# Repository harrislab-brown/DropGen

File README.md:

## Welcome to DropGen! A droplet on demand generator for research applications developed in the Harris Lab at Brown University

DropGen uses a fluid reservoir and a piezoelectric buzzer to precisely and repeatably dispense small droplets on demand. 
This new version of the Harris Lab DropGen is designed to be 3D printed using filament based FDM printers. Harris Lab has developed a custom printed circuit board to make assembly and use of DropGen as easy as possible, including adding the ability to control the height of DropGen with a commonly available stepper motor driven linear actuator. 

### WIKI:
Complete build documentation and user guide for DropGen can be found under the [Wiki](https://github.com/harrislab-brown/Filament_DropGen/wiki) tab of this repository.

### CAD: 
The CAD directory contains design files for the droplet generator 3D printed parts and the custom PCB. 
Cad files are available as a .f3z Fusion360 archive file, as well as program agnostic .step files for modification in parametric cad software. All parts that require 3D printing are also available in .stl format which can be used with all modern 3D printing slicers. 

The DropGenPCB directory contains project files for the printed circuit board. The PCB was designed using KiCad 8. Production files ready to send to JLCPCB are available here as well (see wiki for details). 

### CODE: 
DropGen is controlled by a web based GUI running on an ESP32-S3 development board. The wiki contains instructions on how to set up the environment required to flash the ESP32 firmware. 

### Documentation: 
This directory contains image and video assets used in the wiki. 

### Credit: 
If you use or adapt the device for academic publication, please cite this repository as well as the preceding works:
* N. Ionkin and D. M. Harris.  Note: A versatile 3D-printed droplet-on-demand generator. Review of Scientific Instruments. 2018; 89 (11) : 116103. [doi.org/10.1063/1.5054400](doi.org/10.1063/1.5054400)
* D. M. Harris, T. Liu and J. W. M. Bush. A low-cost, precise piezoelectric droplet-on-demand generator. Experiments in Fluids. 2015; 56 (4). [dx.doi.org/10.1007/s00348-015-1950-6](dx.doi.org/10.1007/s00348-015-1950-6)

Happy building!

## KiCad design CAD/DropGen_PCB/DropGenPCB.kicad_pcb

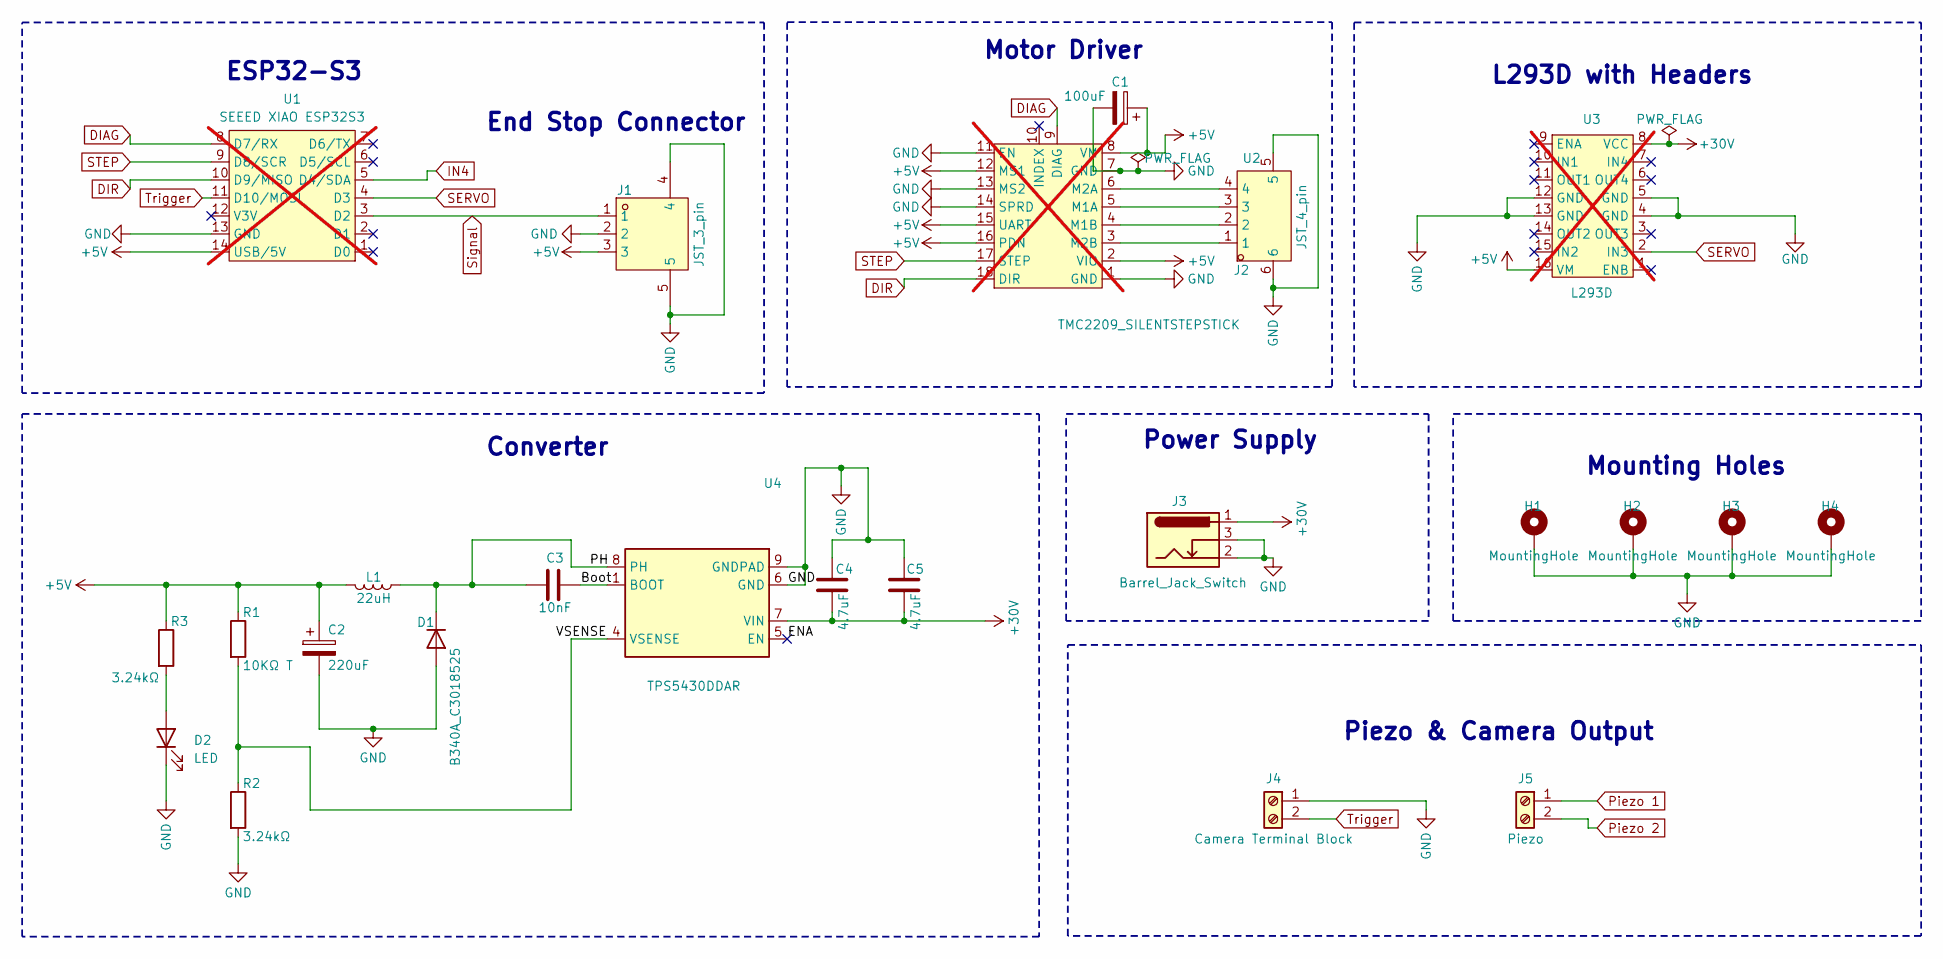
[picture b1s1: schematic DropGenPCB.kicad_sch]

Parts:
C1: 100uF; C_Elec_6.3x7.7; Manufac. Part RVT1V101M0607; LCSC C72478
C2: 220uF; CP_EIA-6032-15_Kemet-U; Manufac. Part TPSC107K010R0100; LCSC C183034
C3: 10nF; C_0805_2012Metric; Manufac. Part 08055C103KAT2A; LCSC C128911
C4, C5: 4.7uF; C_1210_3225Metric; Manufac. Part CS3225X7R106K500NRL; LCSC C2918502
D1: B340A_C3018525; D_SMC; Manufac. Part B560C-13-F; LCSC C85100
D2: LED; LED_0603_1608Metric; Manufac. Part KT-0603R; LCSC C2286
H1, H2, H3, H4: MountingHole; MountingHole_3.2mm_M3_DIN965_Pad
J1: JST_3_pin; 3_pin_jst; Manufac. Part S3B-XH-SM4-TB(LF)(SN); LCSC C5306495
J2: JST_4_pin; 4_pin_jst; Manufac. Part S4B-XH-SM4-TB(LF)(SN); LCSC C161861
J3: Barrel_Jack_Switch; BarrelJack_GCT_DCJ200-10-A_Horizontal; Manufac. Part DC-470-2.1GP; LCSC C194407
J4: Camera Terminal Block; terminal_block; Manufac. Part XY115A-5.0-2P; LCSC C784935
J5: Piezo; terminal_block; Manufac. Part XY115A-5.0-2P; LCSC C784935
L1: 22uH; L_Vishay_IHLP-4040; Manufac. Part IHLP4040DZER220M11; LCSC C845072
R1: 10KΩ T; R_0402_1005Metric_Pad0.72x0.64mm_HandSolder; Manufac. Part RC0201FR-0710KL; LCSC C25744
R2, R3: 3.24kΩ; R_0603_1608Metric; Manufac. Part CRCW06033K24FKEA; LCSC C844165
U1: SEEED XIAO ESP32S3; ESP32S3; Manufac. Part 113991114; not fitted
U2: TMC2209_SILENTSTEPSTICK; MC2209 numbers; Manufac. Part 787794452214; not fitted
U3: L293D; Manufac. Part L293DN; LCSC C434590; not fitted
U4: TPS5430DDAR; TI_SO-PowerPAD-8_ThermalVias; Manufac. Part TPS5430DDAR; LCSC C9864

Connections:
+5V: C1.1, C2.1, J1.3, L1.2, R1.1, R3.1, U1.14 (USB/5V), U2.2 (VIO), U2.8 (VM), U2.12 (MS1), U2.15 (UART), U2.16 (PDN), U3.16 (VM)
+30V: C4.2, C5.2, J3.1, U3.8 (VCC), U4.7 (VIN)
/Boot: C3.2, U4.1 (BOOT)
/ENA: U4.5 (EN)
/PH: C3.1, D1.1 (K), L1.1, U4.8 (PH)
/VSENSE: R1.2, R2.1, U4.4 (VSENSE)
DIAG: U1.8 (D7/RX), U2.9 (DIAG)
DIR: U1.10 (D9/MISO), U2.18 (DIR)
GND: C1.2, C2.2, C4.1, C5.1, D1.2 (A), D2.1 (K), H1.1, H2.1, H3.1, H4.1, J1.2, J1.4, J1.5, J2.5, J2.6, J3.2, J3.3, J4.1, R2.2, U1.13 (GND), U2.1 (GND), U2.7 (GND), U2.11 (EN), U2.13 (MS2), U2.14 (SPRD), U3.4 (GND), U3.5 (GND), U3.12 (GND), U3.13 (GND), U4.6 (GND), U4.9 (GNDPAD)
IN4: U1.5 (D4/SDA)
unnamed: D2.2 (A), R3.2
unnamed: J2.3, U2.5 (M1A)
unnamed: J2.2, U2.4 (M1B)
unnamed: J2.4, U2.6 (M2A)
unnamed: J2.1, U2.3 (M2B)
Piezo 1: J5.1
Piezo 2: J5.2
SERVO: U1.4 (D3), U3.2 (IN3)
STEP: U1.9 (D8/SCR), U2.17 (STEP)
Signal: J1.1, U1.3 (D2)
Trigger: J4.2, U1.11 (D10/MOSI)

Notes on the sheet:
Mounting Holes
ESP32-S3
Converter
Motor Driver
End Stop Connector
Piezo & Camera Output
L293D with Headers
Power Supply

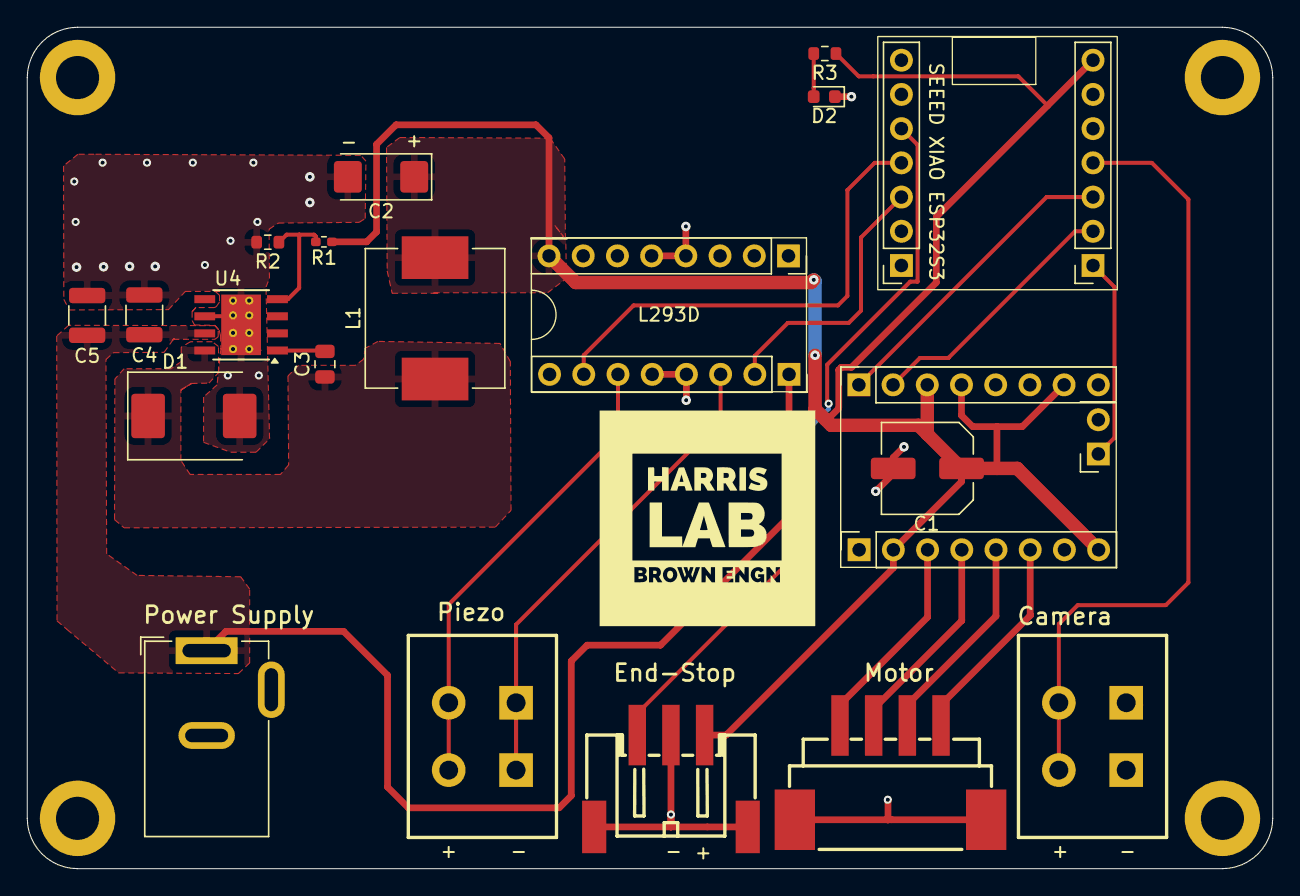
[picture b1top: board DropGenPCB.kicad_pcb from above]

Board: 2 copper layers, 92.5 x 62.5 mm, 24 parts (0 on the bottom side), 17 nets.

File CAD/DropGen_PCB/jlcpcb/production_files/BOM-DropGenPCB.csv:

Comment,Designator,Footprint,LCSC,Quantity
100uF,C1,C_Elec_6.3x7.7,C72478,1
10KΩ T,R1,R_0402_1005Metric_Pad0.72x0.64mm_HandSolder,C25744,1
10nF,C3,C_0805_2012Metric,C128911,1
220uF,C2,CP_EIA-6032-15_Kemet-U,C183034,1
22uH,L1,L_Vishay_IHLP-4040,C845072,1
3.24kΩ,"R2,R3",R_0603_1608Metric,C844165,2
4.7uF,"C4,C5",C_1210_3225Metric,C2918502,2
B340A_C3018525,D1,D_SMC,C85100,1
Barrel_Jack_Switch,J3,BarrelJack_GCT_DCJ200-10-A_Horizontal,C194407,1
Camera Terminal Block,J4,terminal_block,C784935,1
JST_3_pin,J1,3_pin_jst,C5306495,1
JST_4_pin,J2,4_pin_jst,C161861,1
LED,D2,LED_0603_1608Metric,C2286,1
Piezo,J5,terminal_block,C784935,1
TPS5430DDAR,U4,TI_SO-PowerPAD-8_ThermalVias,C9864,1

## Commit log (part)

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2024-07-25 changed how motor run command is called
2024-07-29 changed homing sequence. Emergency stop no longer works...
2024-07-29 drop number now works! need to make button color reset when drops are finished
2024-07-31 fixed camera triggering (wrong pin map)
2024-09-05 changed repository file structure
2024-11-20 changed folder naming, added 3d print screenshots
2024-11-20 added pcb and endstop photos
2024-12-02 added UI diagram
2025-09-03 updated cad files with M6 revision
